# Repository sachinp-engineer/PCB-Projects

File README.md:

# 🔌 PCB Design Projects

Welcome to my PCB Design Projects repository! This repository contains a collection of printed circuit board (PCB) designs created using **KiCad**. Each project includes the schematic, PCB layout, 3D renders, and project documentation.

---

## 👨‍💻 About Me

Hi, I'm **Sachin P**, an Electrical and Electronics Engineering (EEE) student with a strong interest in:

- ⚡ Power Electronics
- 🔋 DC-DC Converters
- 📐 PCB Design
- 🤖 Embedded Systems
- 🌐 IoT Applications

This repository showcases my learning journey in PCB design and electronic hardware development.

---

## 📂 Repository Structure

```
PCB-Projects/
│
├── Boost-Converter/
│   ├── README.md
│   ├── KiCad Files
│   ├── PCB Layout
│   ├── Schematic
│   └── 3D Images
│
├── Buck-Boost-Converter/
│   ├── README.md
│   ├── KiCad Files
│   ├── PCB Layout
│   ├── Schematic
│   └── 3D Images
│
├── Future-Project-3/
├── Future-Project-4/
│
└── README.md
```

---

# 📌 Projects

## ⚡ 1. Boost Converter PCB

A DC-DC Boost Converter designed using KiCad that steps up a lower DC input voltage to a higher output voltage.

### Features

- LM555 PWM Generator
- IRF540N MOSFET Driver
- Compact PCB Layout
- Single-Layer PCB
- 3D PCB Model

📁 Folder:
```
Boost-Converter/
```

---

## ⚡ 2. Buck-Boost Converter PCB

A DC-DC Buck-Boost Converter capable of both stepping up and stepping down the input voltage using PWM control.

### Features

- Dual LM555 PWM Circuits
- IRF540N MOSFET
- Multiple Inductor Stages
- Compact PCB Design
- 3D PCB Visualization

📁 Folder:
```
Buck-Boost-Converter/
```

---

## 🛠 Software Used

- KiCad
- KiCad PCB Editor
- KiCad Schematic Editor
- KiCad 3D Viewer

---

## 📚 Skills Demonstrated

- PCB Design
- Schematic Capture
- Component Footprint Selection
- PCB Routing
- Design Rule Check (DRC)
- 3D PCB Visualization
- Power Electronics Design
- DC-DC Converter Design

---

## 📦 Repository Contents

Each project contains:

- 📄 README.md
- 📐 Schematic Design
- 🖥 PCB Layout
- 📷 3D PCB Images
- 📁 KiCad Project Files
- 📦 Gerber Files *(coming soon)*
- 📋 Bill of Materials *(coming soon)*

---

## 🚀 Future Projects

This repository will continue to grow with more PCB designs, including:

- 🔋 Battery Management System (BMS)
- ⚡ Buck Converter
- 🔌 Flyback Converter
- 🔋 Battery Charger
- 🌞 Solar Charge Controller
- 🔥 Motor Driver PCB
- 🤖 ESP32 Development Board
- 📡 IoT Sensor Interface PCB

---

## 📈 Learning Objectives

- Improve PCB layout techniques
- Design reliable power electronic circuits
- Develop manufacturable PCB designs
- Learn high-current routing and thermal management
- Build a professional hardware engineering portfolio

---

## 🤝 Contributions

Suggestions and feedback are always welcome. Feel free to open an issue or submit a pull request.

---

## 📜 License

This repository is licensed under the **MIT License**.

---

## ⭐ Support

If you find these projects useful, consider giving this repository a ⭐ on GitHub!

---

## 📬 Contact

**Sachin P**

🎓 Electrical and Electronics Engineering Student

💡 Interests:
- PCB Design
- Embedded Systems
- Power Electronics
- IoT
- Hardware Development

Happy Designing! ⚡

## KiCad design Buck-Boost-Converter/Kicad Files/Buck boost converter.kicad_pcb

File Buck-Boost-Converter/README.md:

# ⚡ Buck-Boost Converter PCB Design

A PCB implementation of a DC-DC Buck-Boost Converter designed using KiCad.

This converter can either increase (boost) or decrease (buck) the input voltage depending on the operating conditions.

---

## 📌 Project Overview

This project includes:

- Dual PWM Signal Generator using LM555 Timer ICs
- Buck-Boost Converter Stage
- MOSFET Switching Circuit
- Compact PCB Layout
- 3D PCB Design

---

## 🛠 Software Used

- KiCad 9
- PCB Editor
- Schematic Editor
- 3D Viewer

---

## 🔧 Components Used

- LM555 Timer IC (2x)
- IRF540N MOSFET
- Inductors
- Fast Recovery Diodes
- Electrolytic Capacitors
- Ceramic Capacitors
- Potentiometers
- Resistors
- Terminal Connectors

---

## 📷 Project Images

### Schematic

---

### PCB Layout

---

### 3D View

---

### 3D Render

---

## ⚙ Working Principle

- Generates PWM signals using LM555 timer circuits.
- Controls IRF540N MOSFET switching.
- Operates in Buck mode when output voltage is lower than input.
- Operates in Boost mode when output voltage is higher than input.
- Smooth output voltage using inductors and capacitors.

---

## 📂 Files Included

- KiCad Schematic
- PCB Layout
- 3D PCB Images
- Gerber Files *(optional)*
- Bill of Materials *(optional)*

---

## 🚀 Features

- Dual PWM Control
- Compact PCB Design
- Through-hole MOSFET Mounting
- Easy Manufacturing
- 3D Visualization

---

## 🎯 Applications

- Battery Charging
- Solar Power Systems
- Embedded Electronics
- Automotive Electronics
- Portable Power Supplies

---

## 👨‍💻 Author

Sachin P

Electrical and Electronics Engineering Student

Interested in PCB Design, Embedded Systems, IoT and Power Electronics.

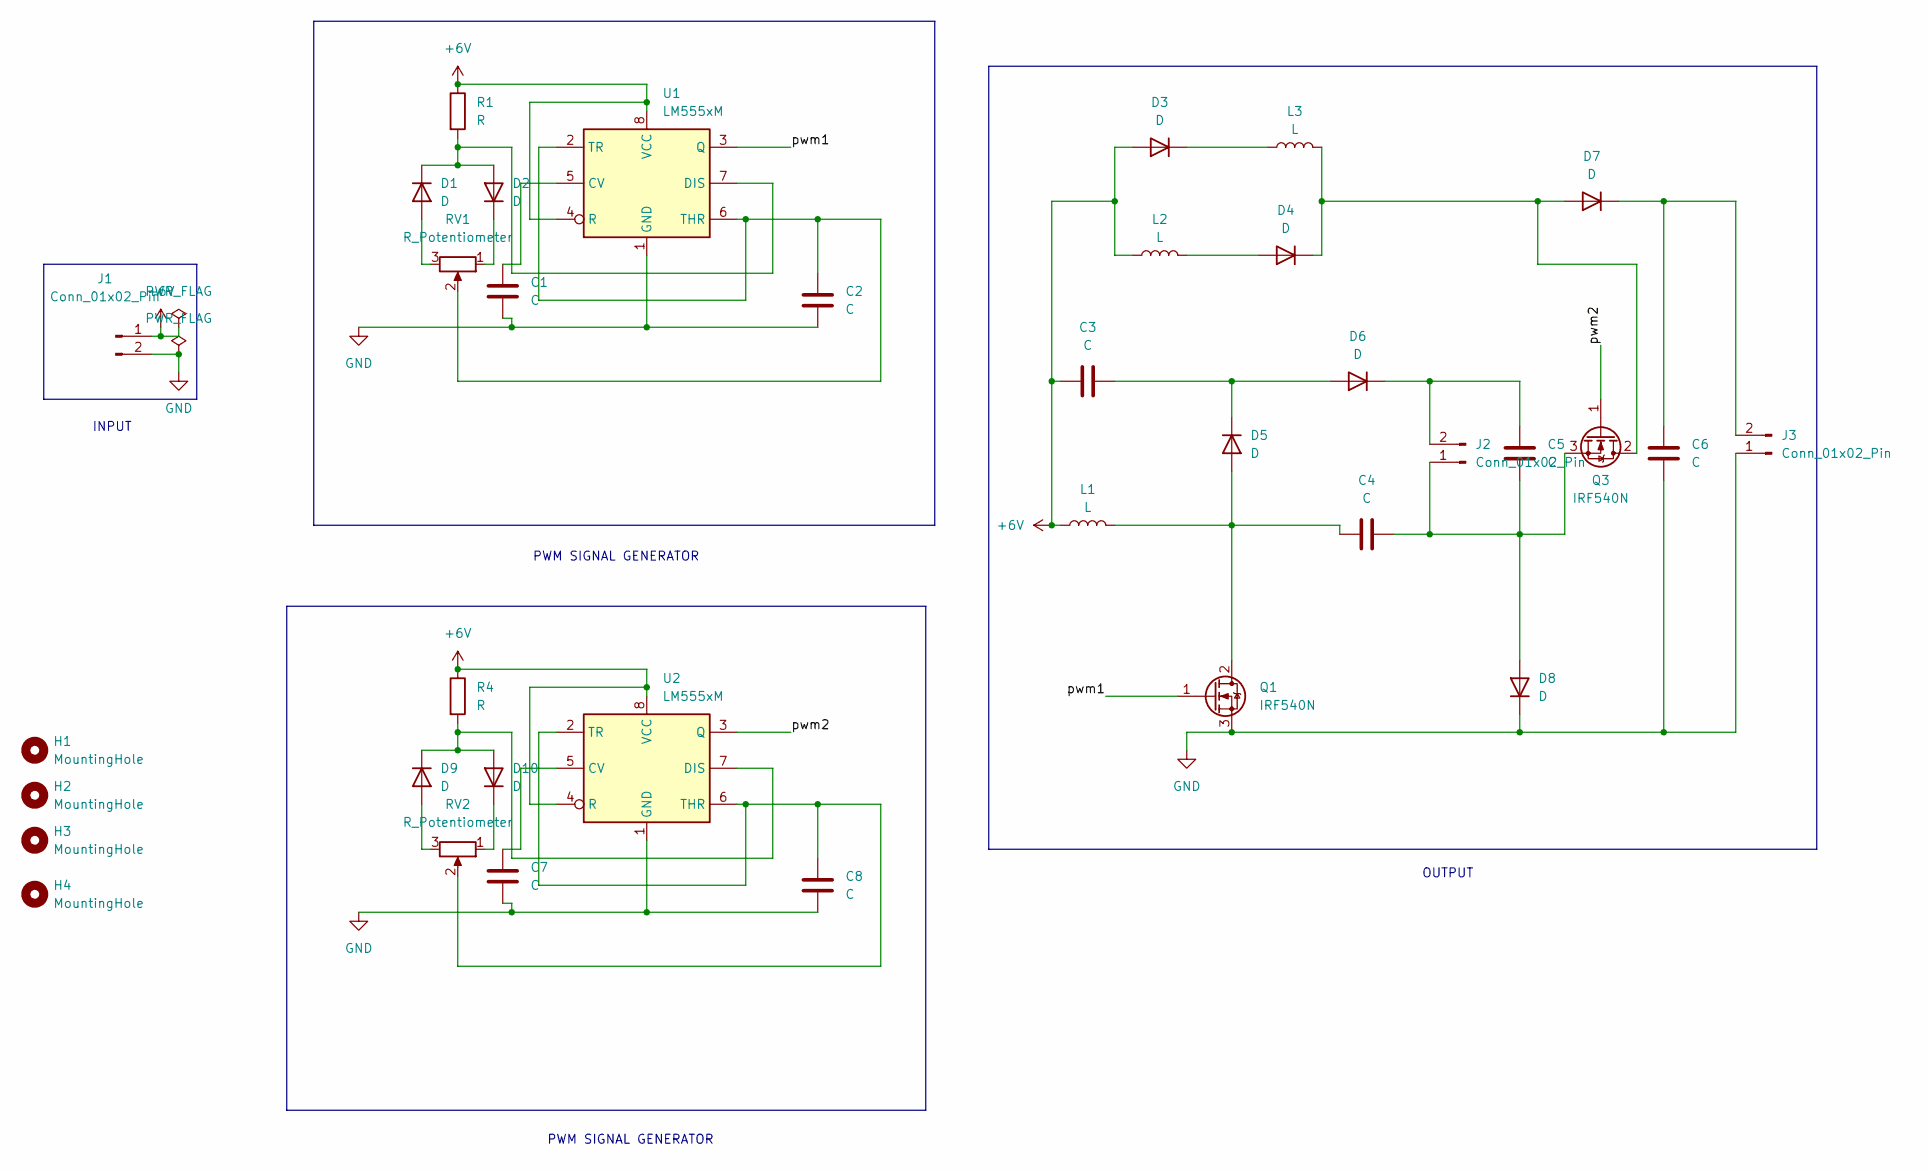
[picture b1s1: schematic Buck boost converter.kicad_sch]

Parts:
C1, C2, C3, C4, C5, C6, C7, C8: C; C_0805_2012Metric_Pad1.18x1.45mm_HandSolder
D1, D2, D3, D4, D5, D6, D7, D8, D9, D10: D; D_SOD-123F
H1, H2, H3, H4: MountingHole; MountingHole_2.2mm_M2
J1, J2, J3: Conn_01x02_Pin; JST_XH_B2B-XH-AM_1x02_P2.50mm_Vertical
L1, L2, L3: L; L_Axial_L5.0mm_D3.6mm_P10.00mm_Horizontal_Murata_BL01RN1A2A2
Q1, Q3: IRF540N; TO-220-3_Vertical
R1, R4: R; R_1206_3216Metric_Pad1.30x1.75mm_HandSolder
RV1, RV2: R_Potentiometer; Potentiometer_TT_P0915N
U1, U2: LM555xM; SOIC-8_3.9x4.9mm_P1.27mm

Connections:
+6V: C3.1, D3.2 (A), J1.1, L1.1, L2.1, R1.1, R4.1, U1.4 (R), U1.8 (VCC), U2.4 (R), U2.8 (VCC)
/pwm1: Q1.1 (G), U1.3 (Q)
/pwm2: Q3.1 (G), U2.3 (Q)
GND: C1.2, C2.2, C6.2, C7.2, C8.2, D8.1 (K), J1.2, J3.1, Q1.3 (S), U1.1 (GND), U2.1 (GND)
unnamed: D1.2 (A), RV1.3
unnamed: D1.1 (K), D2.2 (A), R1.2, U1.7 (DIS)
unnamed: D2.1 (K), RV1.1
unnamed: D3.1 (K), L3.1
unnamed: D4.2 (A), L2.2
unnamed: D4.1 (K), D7.2 (A), L3.2, Q3.2 (D)
unnamed: C4.1, D5.2 (A), L1.2, Q1.2 (D)
unnamed: C3.2, D5.1 (K), D6.2 (A)
unnamed: C5.1, D6.1 (K), J2.2
unnamed: C6.1, D7.1 (K), J3.2
unnamed: C4.2, C5.2, D8.2 (A), J2.1, Q3.3 (S)
unnamed: D9.2 (A), RV2.3
unnamed: D9.1 (K), D10.2 (A), R4.2, U2.7 (DIS)
unnamed: D10.1 (K), RV2.1
unnamed: C1.1, U1.5 (CV)
unnamed: C2.1, RV1.2, U1.2 (TR), U1.6 (THR)
unnamed: C7.1, U2.5 (CV)
unnamed: C8.1, RV2.2, U2.2 (TR), U2.6 (THR)

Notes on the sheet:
INPUT
OUTPUT
PWM SIGNAL GENERATOR

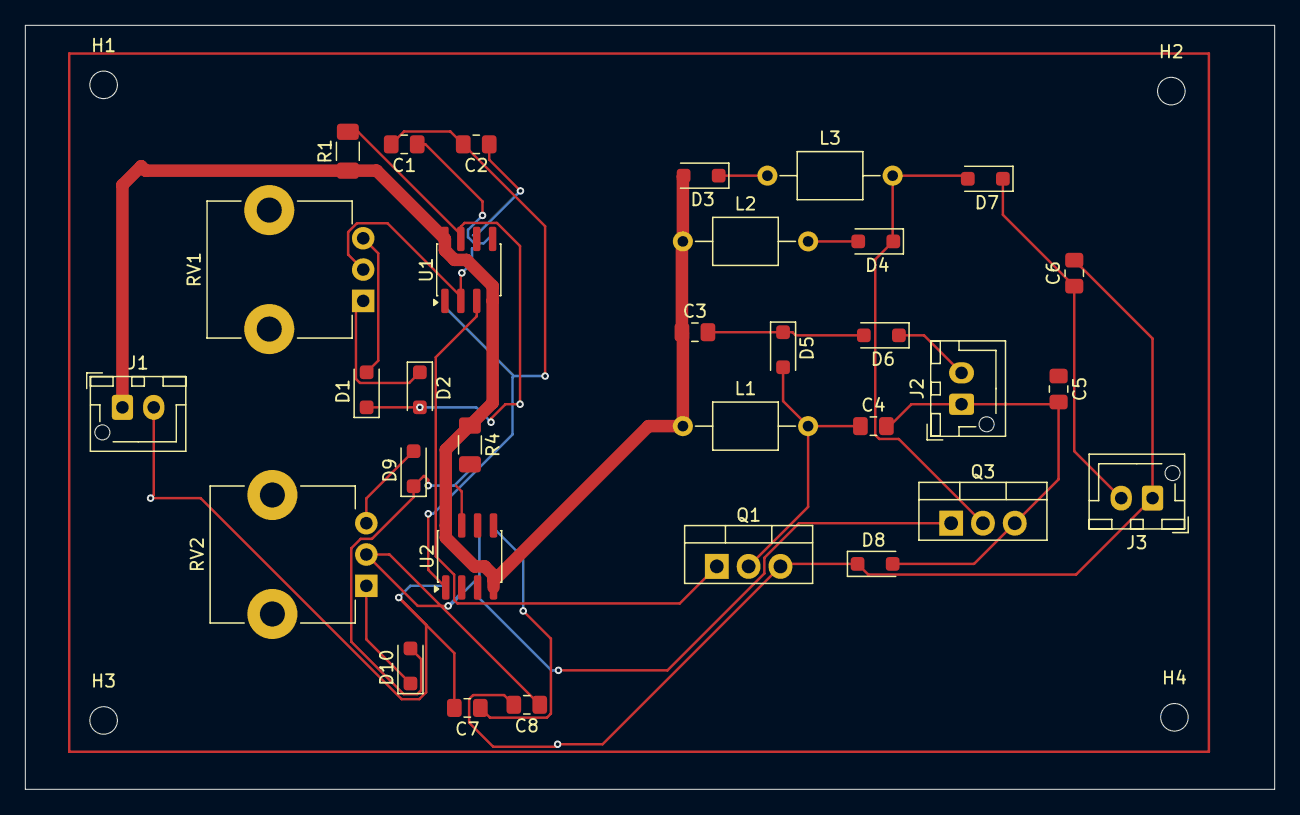
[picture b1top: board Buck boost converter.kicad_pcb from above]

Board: 2 copper layers, 99.8 x 61.0 mm, 36 parts (0 on the bottom side), 22 nets.
